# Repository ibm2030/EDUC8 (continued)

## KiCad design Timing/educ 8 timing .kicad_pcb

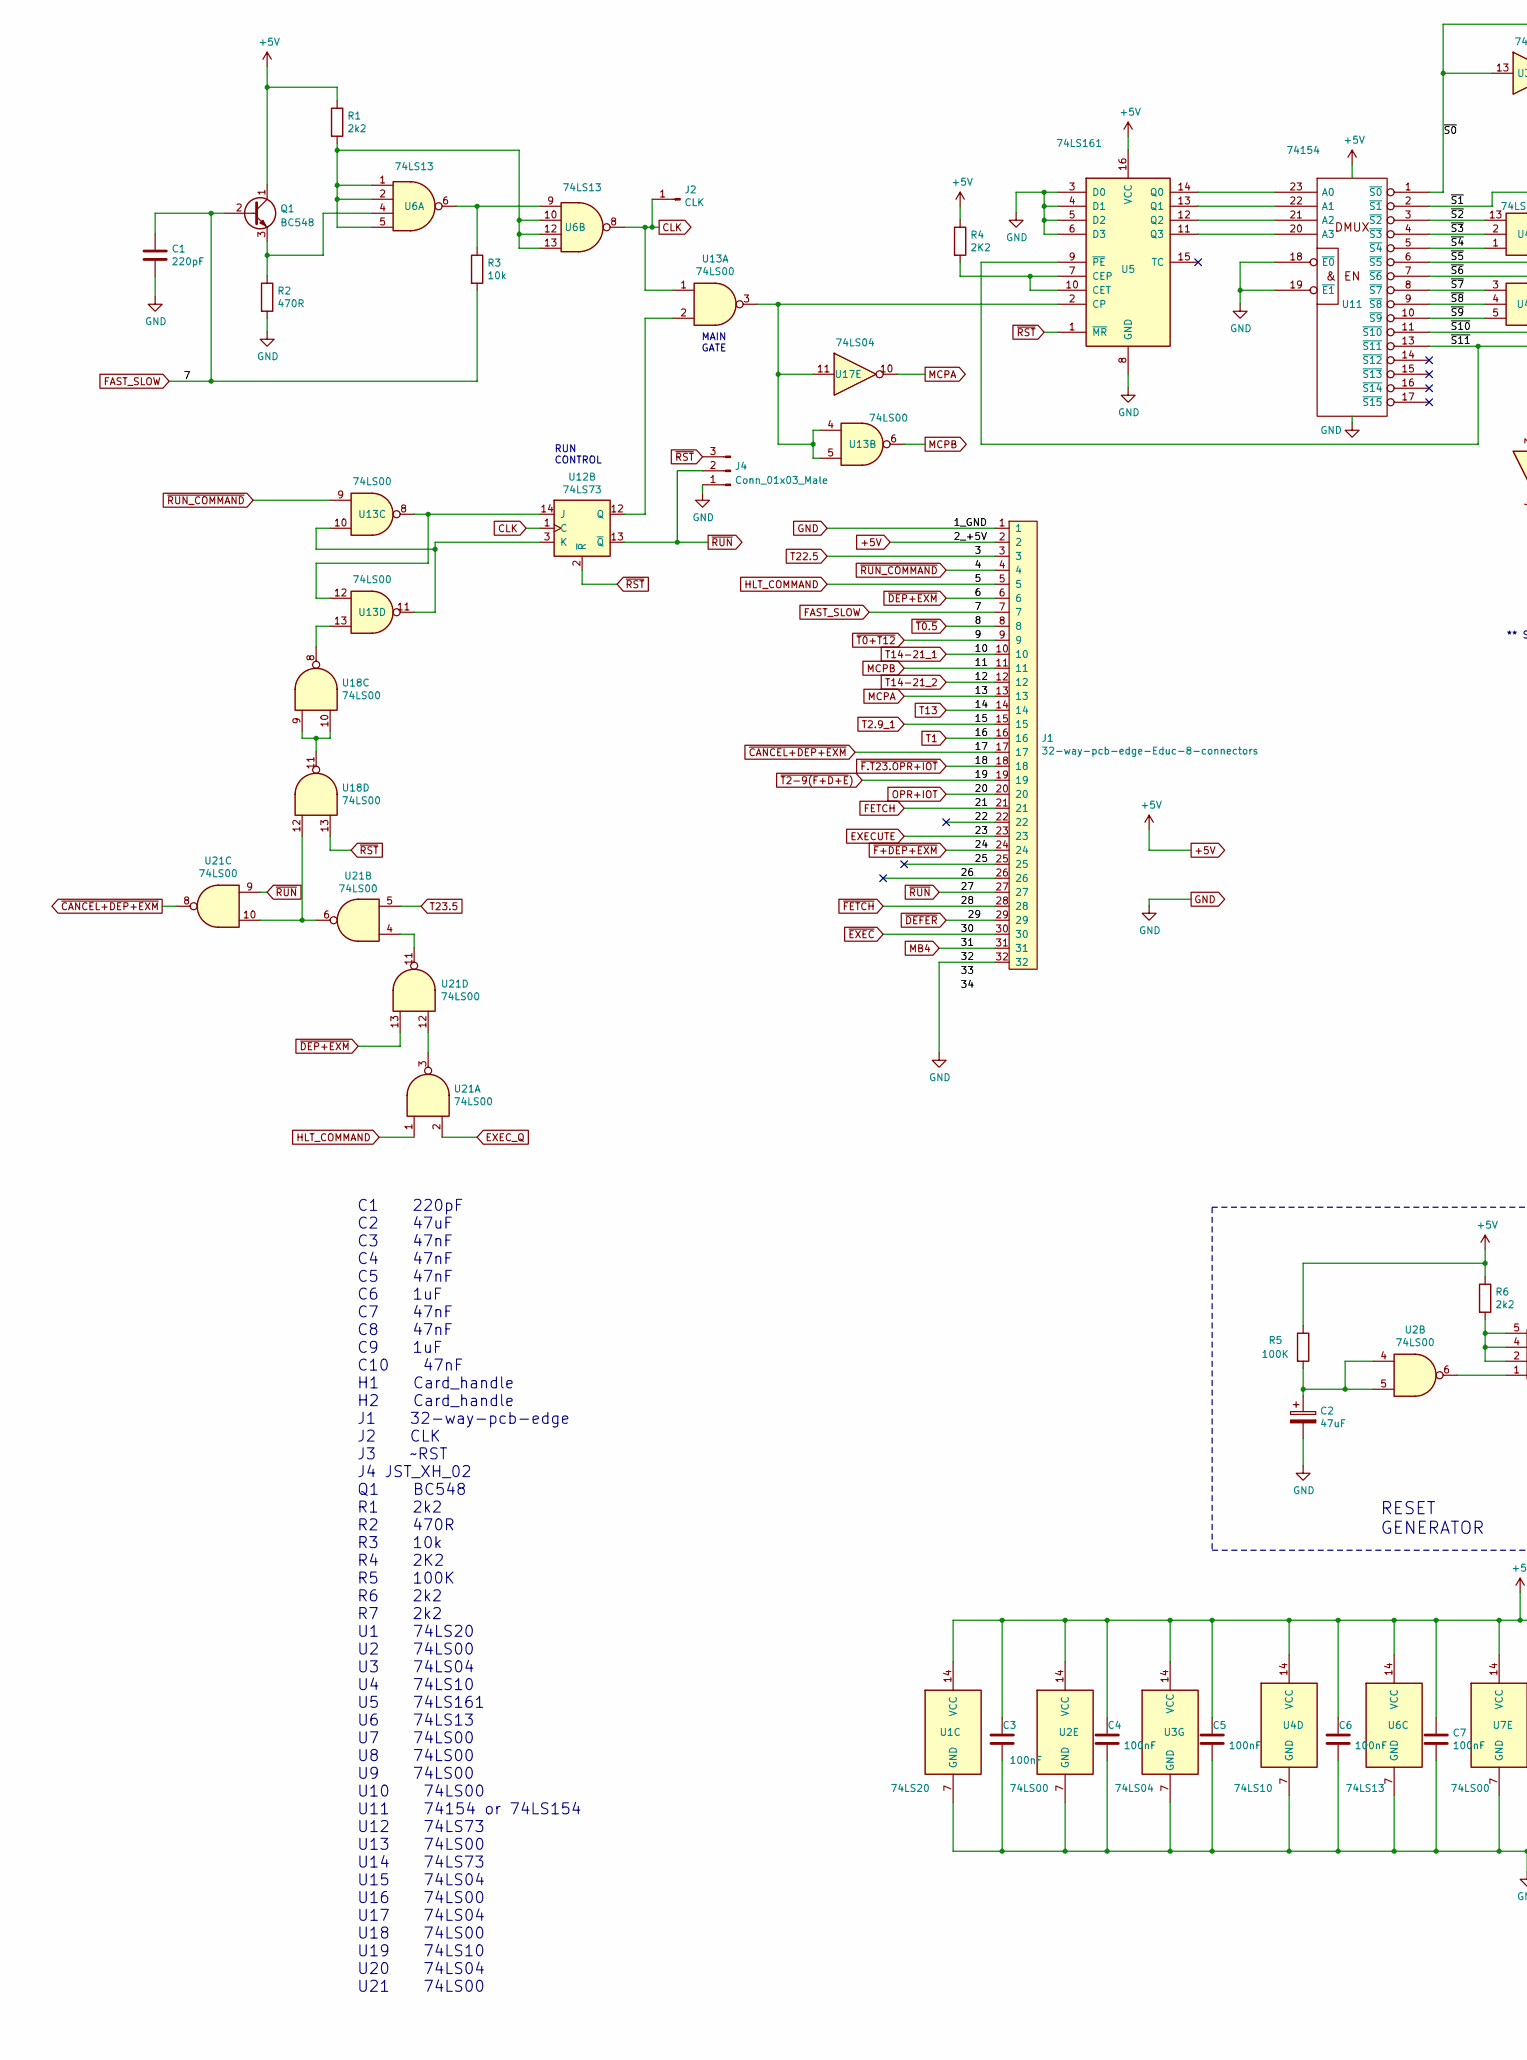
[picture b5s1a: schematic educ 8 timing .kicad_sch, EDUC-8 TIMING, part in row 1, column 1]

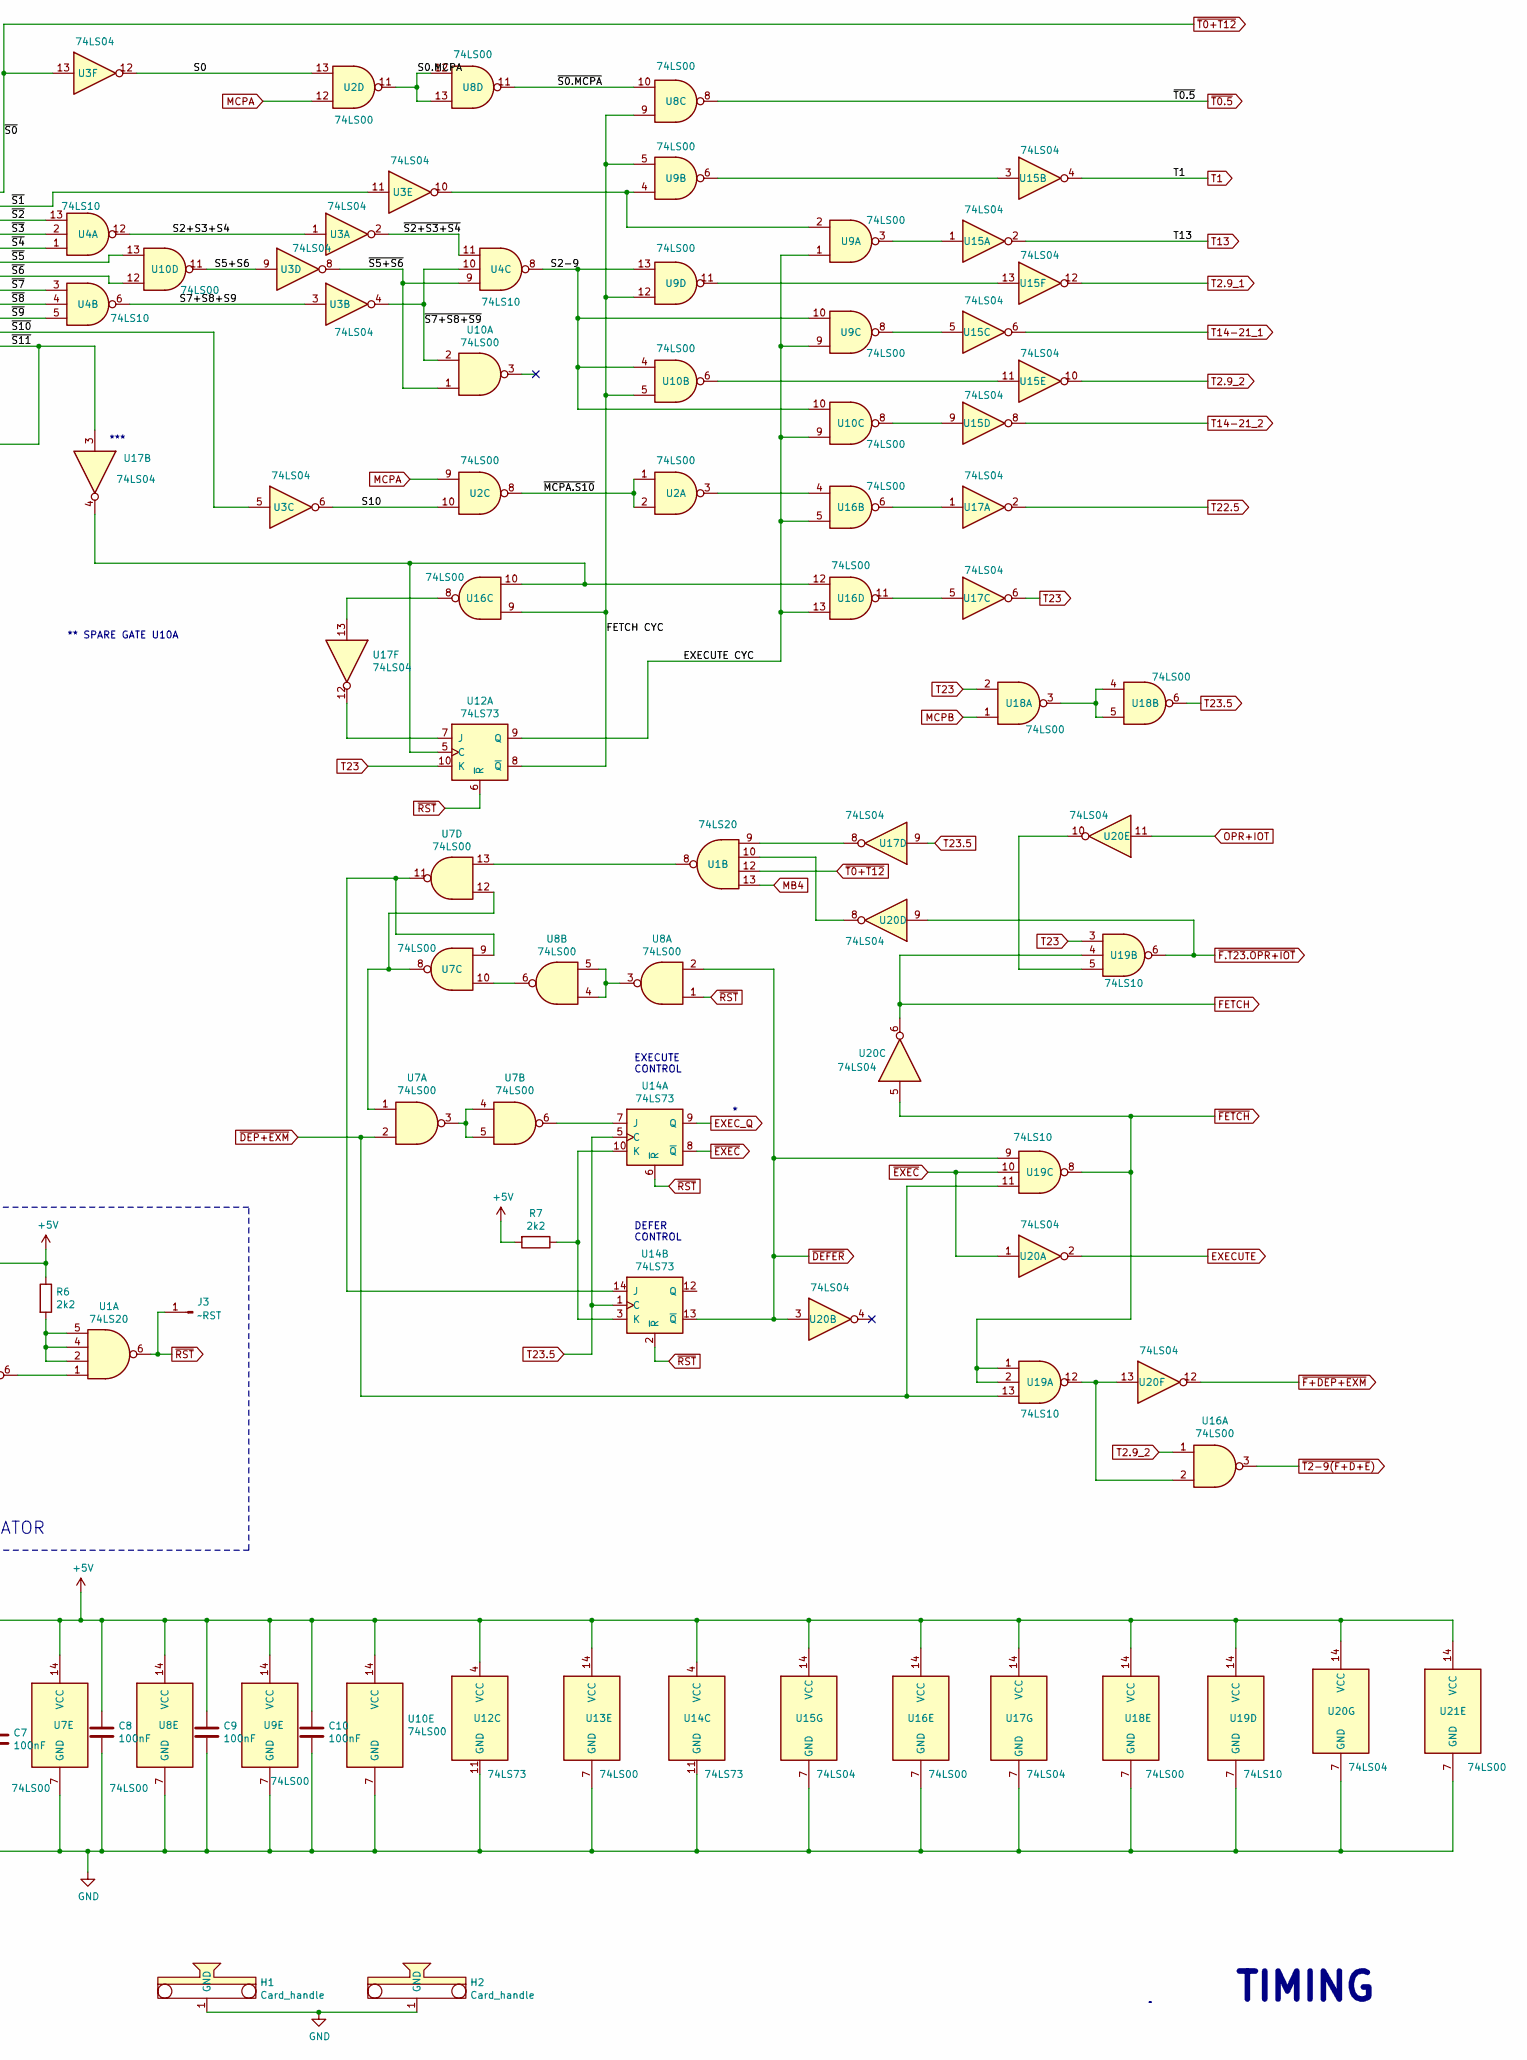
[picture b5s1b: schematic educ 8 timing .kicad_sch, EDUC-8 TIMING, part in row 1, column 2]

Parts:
C1: 220pF; C_Disc_D7.0mm_W2.5mm_P5.00mm
C2: 47uF; CP_Radial_D6.3mm_P2.50mm
C3, C6, C9, C10: 100nF; C_Disc_D5.0mm_W2.5mm_P5.00mm
C4, C5, C7, C8: 100nF; C_Disc_D7.0mm_W2.5mm_P5.00mm
H1, H2: Card_handle
J1: 32-way-pcb-edge-Educ-8-connectors; PCB_32pin
J2: CLK; Pin_D1.0mm_L10.0mm
J3: ~RST; Pin_D1.0mm_L10.0mm
J4: Conn_01x03_Male; JST_XH_B3B-XH-A_1x03_P2.50mm_Vertical
Q1: BC548; TO-92_Wide
R1, R6, R7: 2k2; R_Axial_DIN0309_L9.0mm_D3.2mm_P12.70mm_Horizontal
R2: 470R; R_Axial_DIN0309_L9.0mm_D3.2mm_P12.70mm_Horizontal
R3: 10k; R_Axial_DIN0309_L9.0mm_D3.2mm_P12.70mm_Horizontal
R4: 2K2; R_Axial_DIN0309_L9.0mm_D3.2mm_P12.70mm_Horizontal
R5: 100K; R_Axial_DIN0309_L9.0mm_D3.2mm_P12.70mm_Horizontal
U1: 74LS20; DIP-14_W7.62mm_LongPads
U2, U7, U8, U9, U10, U13, U16, U18, U21: 74LS00; DIP-14_W7.62mm_LongPads
U3, U15, U17, U20: 74LS04; DIP-14_W7.62mm_LongPads
U4, U19: 74LS10; DIP-14_W7.62mm_LongPads
U5: 74LS161; DIP-16_W7.62mm_LongPads
U6: 74LS13; DIP-14_W7.62mm_LongPads
U11: 74154; DIP-24_W15.24mm_LongPads
U12, U14: 74LS73; DIP-14_W7.62mm_LongPads

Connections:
+5V: C3.1, C4.1, C5.1, C6.1, C7.1, C8.1, C9.1, C10.1, J1.2, Q1.1 (C), R1.1, R4.1, R5.1, R6.1, R7.2, U1.14 (VCC), U2.14 (VCC), U3.14 (VCC), U4.14 (VCC), U5.16 (VCC), U6.14 (VCC), U7.14 (VCC), U8.14 (VCC), U9.14 (VCC), U10.14 (VCC), U11.24 (VCC), U12.4 (VCC), U13.14 (VCC), U14.4 (VCC), U15.14 (VCC), U16.14 (VCC), U17.14 (VCC), U18.14 (VCC), U19.14 (VCC), U20.14 (VCC), U21.14 (VCC)
/22: J1.22
/25: J1.25
/26: J1.26
/EXECUTE CYC: U9.1, U9.9, U10.9, U12.9 (Q), U16.5, U16.13
/FETCH CYC: U8.9, U9.5, U9.12, U10.5, U12.8 (~Q), U16.9
/S0: U2.13, U3.12
/S0.MCPA: U2.11, U8.12, U8.13
/S2+S3+S4: U3.1, U4.12
/S2-9: U4.8, U9.10, U9.13, U10.4, U10.10
/S5+S6: U3.9, U10.11
/S7+S8+S9: U3.3, U4.6
/S10: U2.10, U3.6
/~MCPA.S10: U2.1, U2.2, U2.8
/~S0.MCPA: U8.10, U8.11
/~S1: U3.11, U11.2 (~S1)
/~S2+S3+S4: U3.2, U4.11
/~S2: U4.13, U11.3 (~S2)
/~S3: U4.2, U11.4 (~S3)
/~S4: U4.1, U11.5 (~S4)
/~S5+S6: U3.8, U4.9, U10.1
/~S5: U10.13, U11.6 (~S5)
/~S6: U10.12, U11.7 (~S6)
/~S7+S8+S9: U3.4, U4.10, U10.2
/~S7: U4.3, U11.8 (~S7)
/~S8: U4.4, U11.9 (~S8)
/~S9: U4.5, U11.10 (~S9)
/~S10: U3.5, U11.11 (~S10)
/~S11: U5.9 (~PE), U11.13 (~S11), U17.3
CLK: J2.1, U6.8, U12.1 (C), U13.1
EXECUTE: J1.23, U20.2
EXEC_Q: U14.9 (Q), U21.2
FAST_SLOW: C1.1, J1.7, Q1.2 (B), R3.2
FETCH: J1.21, U19.4, U20.6
GND: C1.2, C2.2, C3.2, C4.2, C5.2, C6.2, C7.2, C8.2, C9.2, C10.2, H1.1 (GND), H2.1 (GND), J1.1, J1.32, J4.1, R2.2, U1.7 (GND), U2.7 (GND), U3.7 (GND), U4.7 (GND), U5.3 (D0), U5.4 (D1), U5.5 (D2), U5.6 (D3), U5.8 (GND), U6.7 (GND), U7.7 (GND), U8.7 (GND), U9.7 (GND), U10.7 (GND), U11.12 (GND), U11.18 (~E0), U11.19 (~E1), U12.11 (GND), U13.7 (GND), U14.11 (GND), U15.7 (GND), U16.7 (GND), U17.7 (GND), U18.7 (GND), U19.7 (GND), U20.7 (GND), U21.7 (GND)
HLT_COMMAND: J1.5, U21.1
MB4: J1.31, U1.13
MCPA: J1.13, U2.9, U2.12, U17.10
MCPB: J1.11, U13.6, U18.1
unnamed: C2.1, R5.2, U2.4, U2.5
unnamed: Q1.3 (E), R2.1, U6.4
unnamed: R1.2, U6.1, U6.2, U6.5, U6.10, U6.12, U6.13
unnamed: R3.1, U6.6, U6.9
unnamed: R6.2, U1.2, U1.4, U1.5
unnamed: U1.1, U2.6
unnamed: U1.8, U7.13
unnamed: U1.9, U17.8
unnamed: U1.10, U20.8
unnamed: U3.10, U9.2, U9.4
unnamed: R4.2, U5.7 (CEP), U5.10 (CET)
unnamed: U5.2 (CP), U13.3, U13.4, U13.5, U17.11
unnamed: U7.1, U7.8, U7.12
unnamed: U7.3, U7.4, U7.5
unnamed: U7.10, U8.6
unnamed: U8.3, U8.4, U8.5
unnamed: U10.6, U15.11
unnamed: U10.8, U15.9
unnamed: U5.14 (Q0), U11.23 (A0)
unnamed: U5.13 (Q1), U11.22 (A1)
unnamed: U5.12 (Q2), U11.21 (A2)
unnamed: U5.11 (Q3), U11.20 (A3)
unnamed: U12.5 (C), U16.10, U16.12, U17.4
unnamed: U12.7 (J), U17.12
unnamed: U12.14 (J), U13.8, U13.12
unnamed: U12.3 (K), U13.10, U13.11
unnamed: U12.12 (Q), U13.2
unnamed: U13.13, U18.8
unnamed: U7.6, U14.7 (J)
unnamed: R7.1, U14.3 (K), U14.10 (K)
unnamed: U7.9, U7.11, U14.14 (J)
unnamed: U9.3, U15.1
unnamed: U9.6, U15.3
unnamed: U9.8, U15.5
unnamed: U9.11, U15.13
unnamed: U16.2, U19.12, U20.13
unnamed: U2.3, U16.4
unnamed: U16.6, U17.1
unnamed: U16.8, U17.13
unnamed: U16.11, U17.5
unnamed: U18.3, U18.4, U18.5
unnamed: U18.9, U18.10, U18.11
unnamed: U18.12, U21.6, U21.10
unnamed: U19.5, U20.10
unnamed: U21.4, U21.11
unnamed: U21.3, U21.12
OPR+IOT: J1.20, U20.11
T1: J1.16, U15.4
T2.9_1: J1.15, U15.12
T2.9_2: U15.10, U16.1
T13: J1.14, U15.2
T14-21_1: J1.10, U15.6
T14-21_2: J1.12, U15.8
T22.5: J1.3, U17.2
T23: U12.10 (K), U17.6, U18.2, U19.3
T23.5: U14.1 (C), U14.5 (C), U17.9, U18.6, U21.5
~CANCEL+DEP+EXM: J1.17, U21.8
~DEFER: J1.29, U8.2, U14.13 (~Q), U19.9, U20.3
~DEP+EXM: J1.6, U7.2, U19.11, U19.13, U21.13
~EXEC: J1.30, U14.8 (~Q), U19.10, U20.1
~F+DEP+EXM: J1.24, U20.12
~F.T23.OPR+IOT: J1.18, U19.6, U20.9
~FETCH: J1.28, U19.1, U19.2, U19.8, U20.5
~RST: J3.1, J4.3, U1.6, U5.1 (~MR), U8.1, U12.2 (~R), U12.6 (~R), U14.2 (~R), U14.6 (~R), U18.13
~RUN_COMMAND: J1.4, U13.9
~RUN: J1.27, J4.2, U12.13 (~Q), U21.9
~T0+T12: J1.9, U1.12, U3.13, U11.1 (~S0)
~T0.5: J1.8, U8.8
~T2-9(F+D+E): J1.19, U16.3

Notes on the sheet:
RUN CONTROL
DEFER CONTROL
EXECUTE CONTROL
***
TIMING
RESET GENERATOR
** SPARE GATE U10A
C1 220pF C2 47uF C3 47nF C4 47nF C5 47nF C6 1uF C7 47nF C8 47nF C9 1uF C10 47nF H1 Card_handle H2 Card_handle J1 32-way-pcb-edge J2 CLK J3 ~RST J4 JST_XH_02 Q1 BC548 R1 2k2 R2 470R R3 10k R4 2K2 R5 100K R6 2k2 R7 2k2 U1 74LS20 U2 74LS00 U3 74LS04 U4 74LS10 U5 74LS161 U6 74LS13 U7 74LS00 U8 74LS00 U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
MAIN GATE

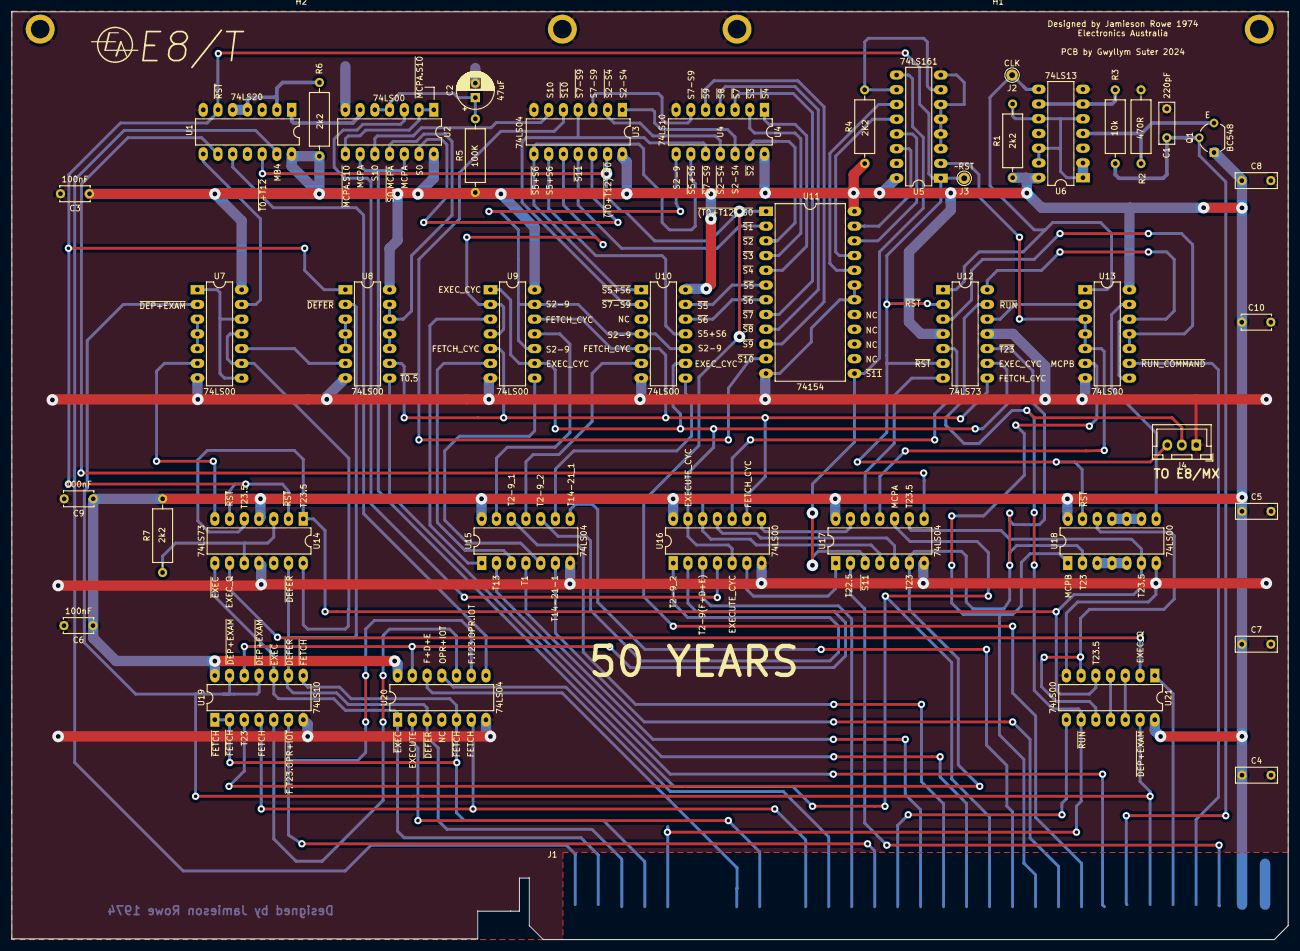
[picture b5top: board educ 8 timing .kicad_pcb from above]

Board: 4 copper layers, 220.0 x 159.9 mm, 45 parts (0 on the bottom side), 105 nets.

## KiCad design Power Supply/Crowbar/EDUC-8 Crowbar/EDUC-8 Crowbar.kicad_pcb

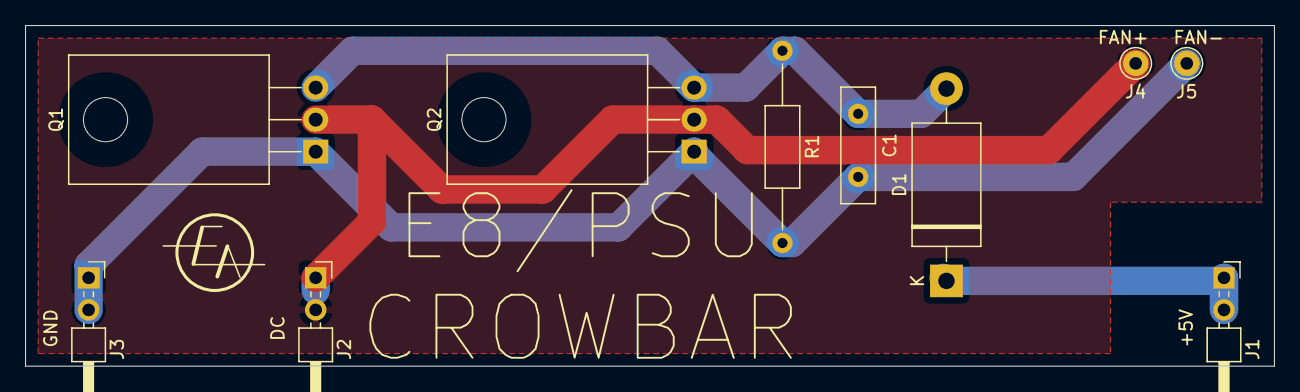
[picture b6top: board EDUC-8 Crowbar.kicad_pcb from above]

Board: 2 copper layers, 99.0 x 27.0 mm, 10 parts (0 on the bottom side), 4 nets.

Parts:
C1: C; C_Disc_D9.0mm_W2.5mm_P5.00mm
D1: 1N5328B; D_DO-201_P15.24mm_Horizontal
J1: +5V; PinHeader_2x01_P2.54mm_Horizontal
J2: DC; PinHeader_2x01_P2.54mm_Horizontal
J3: GND; PinHeader_2x01_P2.54mm_Horizontal
J4: FAN+; Pin_D1.0mm_L10.0mm
J5: FAN-; Pin_D1.0mm_L10.0mm
Q1, Q2: TIC106; TO-220-3_Horizontal_TabDown
R1: R; R_Axial_DIN0207_L6.3mm_D2.5mm_P15.24mm_Horizontal

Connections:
unnamed: C1.1, D1.2, Q1.3, Q2.3, R1.1
unnamed: C1.2, J3.1, J3.2, J5.1, Q1.1, Q2.1, R1.2
unnamed: D1.1, J1.1, J1.2
unnamed: J2.1, J2.2, J4.1, Q1.2, Q2.2

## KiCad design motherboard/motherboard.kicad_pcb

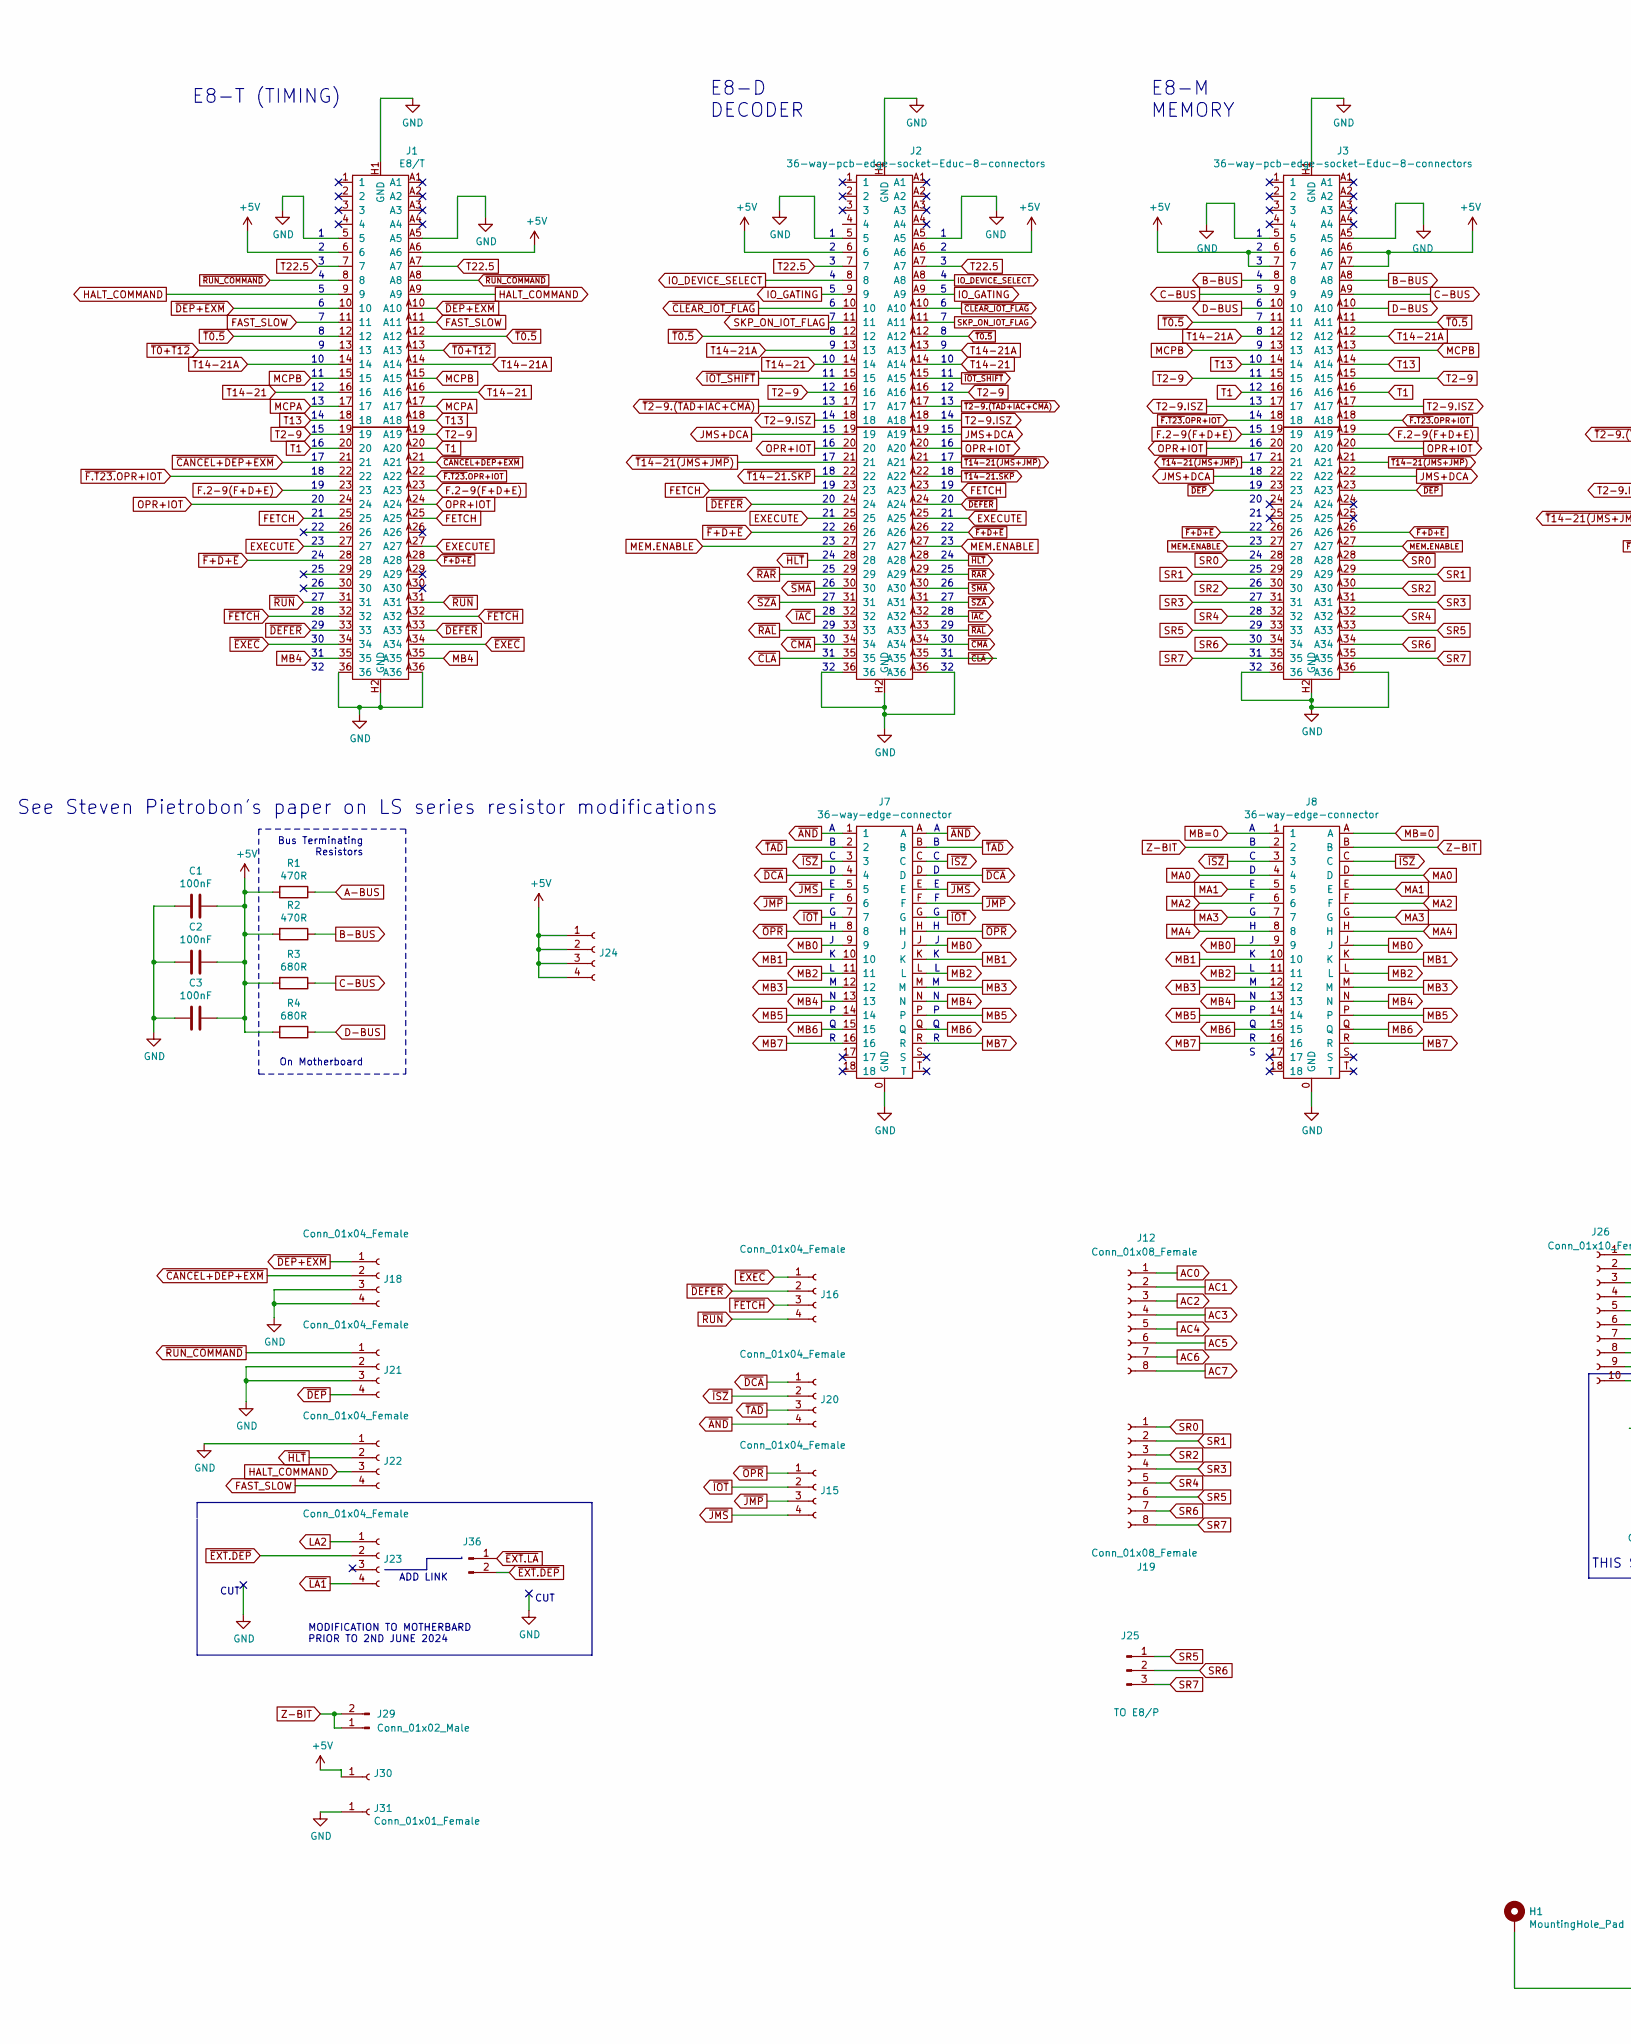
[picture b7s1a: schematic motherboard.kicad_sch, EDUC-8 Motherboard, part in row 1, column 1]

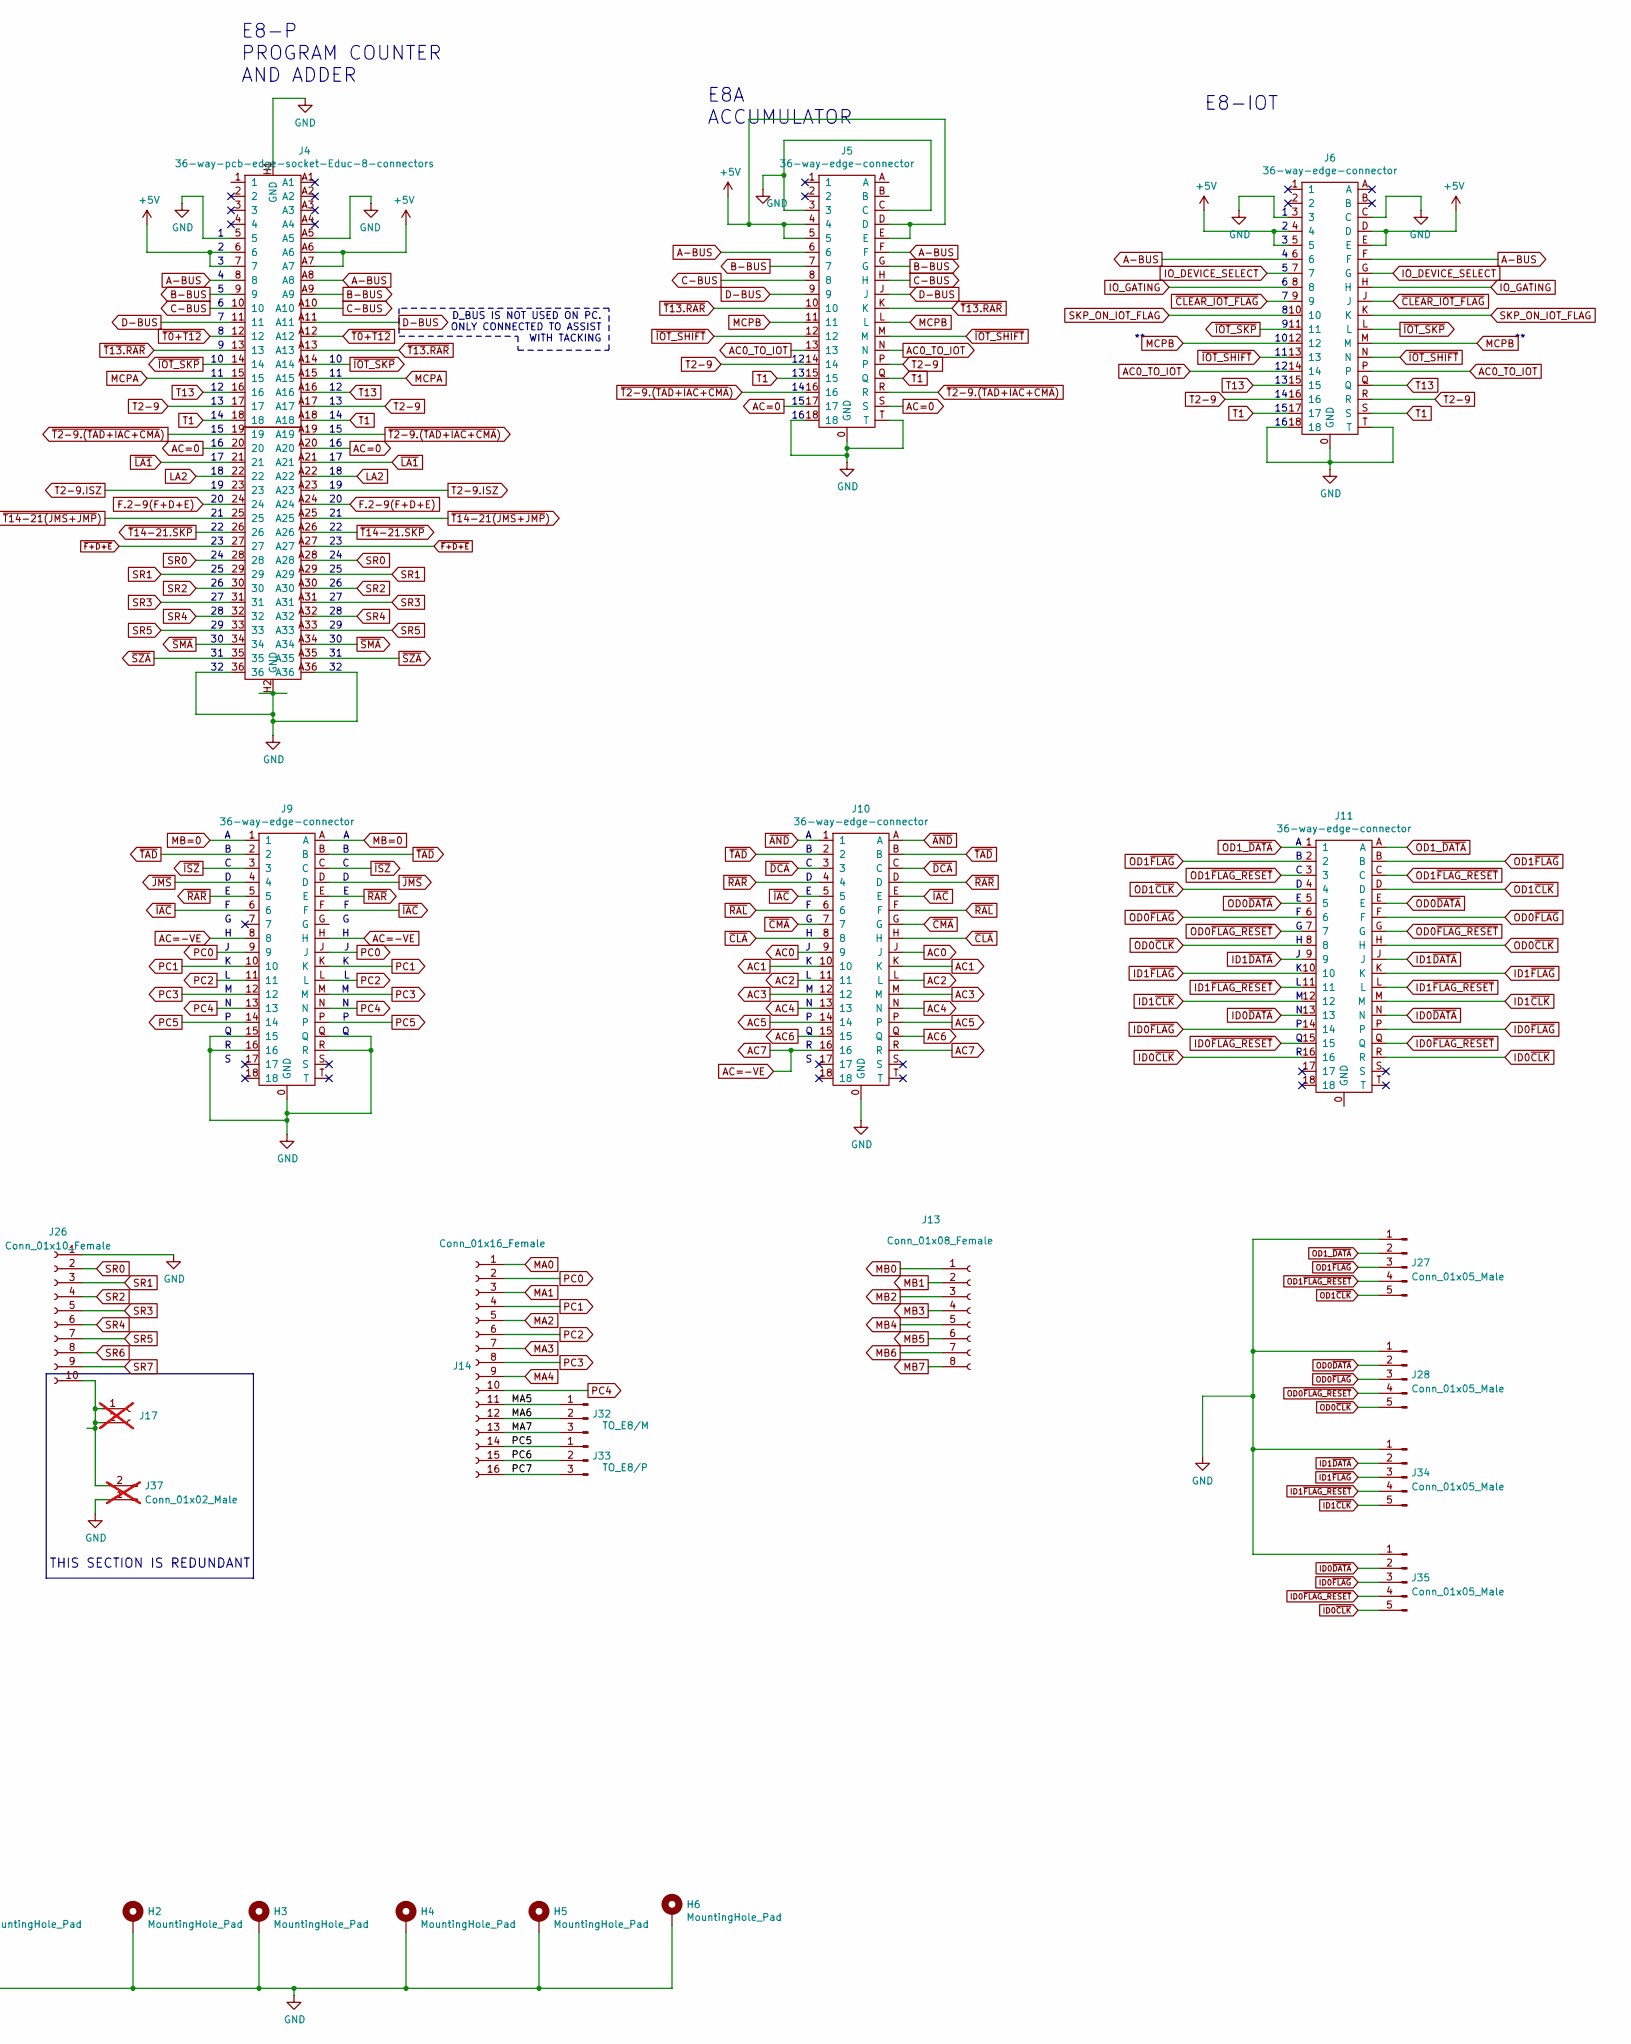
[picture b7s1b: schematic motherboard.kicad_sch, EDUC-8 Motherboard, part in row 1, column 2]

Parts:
C1, C2, C3: 100nF; C_Disc_D8.0mm_W5.0mm_P7.50mm
H1, H2, H3, H4, H5, H6: MountingHole_Pad; MountingHole_3.2mm_M3_Pad_Via
J1: E8/T; 72_way_3.96mm_card_edge_socket
J2, J3, J4: 36-way-pcb-edge-socket-Educ-8-connectors; 72_way_3.96mm_card_edge_socket
J5, J6, J7, J8, J9, J10, J11: 36-way-edge-connector; 36_way_3.96mm_card_edge_socket
J12, J13, J19: Conn_01x08_Female; PinHeader_1x08_P2.54mm_Vertical
J14: Conn_01x16_Female; PinHeader_1x16_P2.54mm_Vertical
J15, J16, J18, J20, J21, J22, J23, J24: Conn_01x04_Female; PinHeader_1x04_P2.54mm_Vertical
J17: Conn_01x02_Female; PinSocket_1x02_P2.54mm_Vertical; not fitted
J25: TO E8/P
J26: Conn_01x10_Female; JST_XH_B10B-XH-AM_1x10_P2.50mm_Vertical
J27, J28, J34, J35: Conn_01x05_Male; JST_XH_B5B-XH-AM_1x05_P2.50mm_Vertical
J29, J36: Conn_01x02_Male; JST_XH_B2B-XH-AM_1x02_P2.50mm_Vertical
J30, J31: Conn_01x01_Female; Pin_D1.2mm_L10.2mm_W2.9mm_FlatFork
J32: TO_E8/M; JST_XA_B03B-XASK-1_1x03_P2.50mm_Vertical
J33: TO_E8/P; JST_XA_B03B-XASK-1_1x03_P2.50mm_Vertical
J37: Conn_01x02_Male; JST_XH_B2B-XH-AM_1x02_P2.50mm_Vertical; not fitted
R1, R2: 470R; R_Axial_DIN0207_L6.3mm_D2.5mm_P10.16mm_Horizontal
R3, R4: 680R; R_Axial_DIN0207_L6.3mm_D2.5mm_P10.16mm_Horizontal

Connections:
+5V: C1.1, C2.1, C3.1, J1.6, J1.A6, J2.6, J2.A6, J3.6, J3.7, J3.A6, J3.A7, J4.6, J4.7, J4.A6, J4.A7, J5.4, J5.5, J5.D, J5.E, J6.4, J6.5, J6.D, J6.E, J24.1, J24.2, J24.3, J24.4, J30.1, R1.2, R2.2, R3.2, R4.2
/MA5: J14.11, J32.1
/MA6: J14.12, J32.2
/MA7: J14.13, J32.3
/PC6: J14.15, J33.2
/PC7: J14.16, J33.3
A-BUS: J4.8, J4.A8, J5.6, J5.F, J6.6, J6.F, R1.1
AC0: J10.9, J10.J, J12.1
AC0_TO_IOT: J5.13, J5.N, J6.14, J6.P
AC1: J10.10, J10.K, J12.2
AC2: J10.11, J10.L, J12.3
AC3: J10.12, J10.M, J12.4
AC4: J10.13, J10.N, J12.5
AC5: J10.14, J10.P, J12.6
AC6: J10.15, J10.Q, J12.7
AC7: J9.8, J9.H, J10.16, J10.R, J12.8
AC=0: J4.20, J4.A20, J5.17, J5.S
B-BUS: J3.8, J3.A8, J4.9, J4.A9, J5.7, J5.G, R2.1
C-BUS: J3.9, J3.A9, J4.10, J4.A10, J5.8, J5.H, R3.1
D-BUS: J3.10, J3.A10, J4.11, J4.A11, J5.9, J5.J, R4.1
EXECUTE: J1.27, J1.A27, J2.25, J2.A25
F.2-9(F+D+E): J1.23, J1.A23, J3.19, J3.A19, J4.24, J4.A24
FAST_SLOW: J1.11, J1.A11, J22.4
FETCH: J1.25, J1.A25, J2.23, J2.A23
GND: C1.2, C2.2, C3.2, H1.1, H2.1, H3.1, H4.1, H5.1, H6.1, J1.5, J1.36, J1.A5, J1.A36, J1.H1 (GND), J1.H2 (GND), J2.5, J2.36, J2.A5, J2.A36, J2.H1 (GND), J2.H2 (GND), J3.5, J3.36, J3.A5, J3.A36, J3.H1 (GND), J3.H2 (GND), J4.5, J4.36, J4.A5, J4.A36, J4.H1 (GND), J4.H2 (GND), J5.0 (GND), J5.3, J5.18, J5.C, J5.T, J6.0 (GND), J6.3, J6.18, J6.C, J6.T, J7.0 (GND), J8.0 (GND), J9.0 (GND), J9.15, J9.16, J9.Q, J9.R, J10.0 (GND), J18.3, J18.4, J21.2, J21.3, J22.1, J26.1, J27.1, J28.1, J31.1, J34.1, J35.1, J37.1
HALT_COMMAND: J1.9, J1.A9, J22.3
ID0~CLK: J11.16, J11.R, J35.5
ID0~DATA: J11.13, J11.N, J35.2
ID0~FLAG_RESET: J11.15, J11.Q, J35.4
ID0~FLAG: J11.14, J11.P, J35.3
ID1~CLK: J11.12, J11.M, J34.5
ID1~DATA: J11.9, J11.J, J34.2
ID1~FLAG_RESET: J11.11, J11.L, J34.4
ID1~FLAG: J11.10, J11.K, J34.3
IO_DEVICE_SELECT: J2.8, J2.A8, J6.7, J6.G
IO_GATING: J2.9, J2.A9, J6.8, J6.H
JMS+DCA: J2.19, J2.A19, J3.22, J3.A22
LA2: J4.22, J4.A22, J23.1
MA0: J8.4, J8.D, J14.1
MA1: J8.5, J8.E, J14.3
MA2: J8.6, J8.F, J14.5
MA3: J8.7, J8.G, J14.7
MA4: J8.8, J8.H, J14.9
MB0: J7.9, J7.J, J8.9, J8.J, J13.1
MB1: J7.10, J7.K, J8.10, J8.K, J13.2
MB2: J7.11, J7.L, J8.11, J8.L, J13.3
MB3: J7.12, J7.M, J8.12, J8.M, J13.4
MB4: J1.35, J1.A35, J7.13, J7.N, J8.13, J8.N, J13.5
MB5: J7.14, J7.P, J8.14, J8.P, J13.6
MB6: J7.15, J7.Q, J8.15, J8.Q, J13.7
MB7: J7.16, J7.R, J8.16, J8.R, J13.8
MB=0: J8.1, J8.A, J9.1, J9.A
MCPA: J1.17, J1.A17, J4.15, J4.A15
MCPB: J1.15, J1.A15, J3.13, J3.A13, J5.11, J5.L, J6.12, J6.M
MEM.ENABLE: J2.27, J2.A27, J3.27, J3.A27
OD0~CLK: J11.8, J11.H, J28.5
OD0~DATA: J11.5, J11.E, J28.2
OD0~FLAG_RESET: J11.7, J11.G, J28.4
OD0~FLAG: J11.6, J11.F, J28.3
OD1_~DATA: J11.1, J11.A, J27.2
OD1~CLK: J11.4, J11.D, J27.5
OD1~FLAG_RESET: J11.3, J11.C, J27.4
OD1~FLAG: J11.2, J11.B, J27.3
OPR+IOT: J1.24, J1.A24, J2.20, J2.A20, J3.20, J3.A20
PC0: J9.9, J9.J, J14.2
PC1: J9.10, J9.K, J14.4
PC2: J9.11, J9.L, J14.6
PC3: J9.12, J9.M, J14.8
PC4: J9.13, J9.N, J14.10
PC5: J9.14, J9.P, J14.14, J33.1
SKP_ON_IOT_FLAG: J2.11, J2.A11, J6.10, J6.K
SR0: J3.28, J3.A28, J4.28, J4.A28, J19.1, J26.2
SR1: J3.29, J3.A29, J4.29, J4.A29, J19.2, J26.3
SR2: J3.30, J3.A30, J4.30, J4.A30, J19.3, J26.4
SR3: J3.31, J3.A31, J4.31, J4.A31, J19.4, J26.5
SR4: J3.32, J3.A32, J4.32, J4.A32, J19.5, J26.6
SR5: J3.33, J3.A33, J4.33, J4.A33, J19.6, J25.1, J26.7
SR6: J3.34, J3.A34, J19.7, J25.2, J26.8
SR7: J3.35, J3.A35, J19.8, J25.3, J26.9
T1: J1.20, J1.A20, J3.16, J3.A16, J4.18, J4.A18, J5.15, J5.Q, J6.17, J6.S
T2-9: J1.19, J1.A19, J2.16, J2.A16, J3.15, J3.A15, J4.17, J4.A17, J5.14, J5.P, J6.16, J6.R
T2-9.ISZ: J2.18, J2.A18, J3.17, J3.A17, J4.23, J4.A23
T13: J1.18, J1.A18, J3.14, J3.A14, J4.16, J4.A16, J6.15, J6.Q
T14-21: J1.16, J1.A16, J2.14, J2.A14
T14-21A: J1.14, J1.A14, J2.13, J2.A13, J3.12, J3.A12
T22.5: J1.7, J1.A7, J2.7, J2.A7
Z-BIT: J8.2, J8.B, J29.1, J29.2
~AND: J7.1, J7.A, J10.1, J10.A, J20.4
~CANCEL+DEP+EXM: J1.21, J1.A21, J18.2
~CLA: J2.35, J2.A35, J10.8, J10.H
~CLEAR_IOT_FLAG: J2.10, J2.A10, J6.9, J6.J
~CMA: J2.34, J2.A34, J10.7, J10.G
~DCA: J7.4, J7.D, J10.3, J10.C, J20.1
~DEFER: J1.33, J1.A33, J2.24, J2.A24, J16.2
~DEP+EXM: J1.10, J1.A10, J18.1
~DEP: J3.23, J3.A23, J21.4
~EXEC: J1.34, J1.A34, J16.1
~EXT.DEP: J23.2, J36.2
~F+D+E: J1.28, J1.A28, J2.26, J2.A26, J3.26, J3.A26, J4.27, J4.A27
~F.T23.OPR+IOT: J1.22, J1.A22, J3.18, J3.A18
~FETCH: J1.32, J1.A32, J16.3
~HLT: J2.28, J2.A28, J22.2
~IAC: J2.32, J2.A32, J9.6, J9.F, J10.5, J10.E
~IOT_SHIFT: J2.15, J2.A15, J5.12, J5.M, J6.13, J6.N
~IOT_SKP: J4.14, J4.A14, J6.11, J6.L
~IOT: J7.7, J7.G, J15.2
~ISZ: J7.3, J7.C, J8.3, J8.C, J9.3, J9.C, J20.2
~JMP: J7.6, J7.F, J15.3
~JMS: J7.5, J7.E, J9.4, J9.D, J15.4
~LA1: J4.21, J4.A21, J23.4
~OPR: J7.8, J7.H, J15.1
~RAL: J2.33, J2.A33, J10.6, J10.F
~RAR: J2.29, J2.A29, J9.5, J9.E, J10.4, J10.D
~RUN_COMMAND: J1.8, J1.A8, J21.1
~RUN: J1.31, J1.A31, J16.4
~SMA: J2.30, J2.A30, J4.34, J4.A34
~SZA: J2.31, J2.A31, J4.35, J4.A35
~T0+T12: J1.13, J1.A13, J4.12, J4.A12
~T0.5: J1.12, J1.A12, J2.12, J2.A12, J3.11, J3.A11
~T2-9.(TAD+IAC+CMA): J2.17, J2.A17, J4.19, J4.A19, J5.16, J5.R
~T13.RAR: J4.13, J4.A13, J5.10, J5.K
~T14-21(JMS+JMP): J2.21, J2.A21, J3.21, J3.A21, J4.25, J4.A25
~T14-21.SKP: J2.22, J2.A22, J4.26, J4.A26
~TAD: J7.2, J7.B, J9.2, J9.B, J10.2, J10.B, J20.3

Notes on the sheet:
On Motherboard
ADD LINK
CUT
E8-D DECODER
E8-M MEMORY
E8-IOT
E8-P PROGRAM COUNTER AND ADDER
D_BUS IS NOT USED ON PC. ONLY CONNECTED TO ASSIST WITH TACKING
THIS SECTION IS REDUNDANT
See Steven Pietrobon's paper on LS series resistor modifications
MODIFICATION TO MOTHERBARD PRIOR TO 2ND JUNE 2024
E8-T (TIMING)
Bus Terminating Resistors
E8A ACCUMULATOR

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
